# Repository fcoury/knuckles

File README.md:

# Knuckles

## Human Written TL;DR

There are a lot of split keyboards out there, but most of the ones that piqued
my interest don't have a number row, and I really like having one. I also
wanted a slim ergo split that feels somewhat like a Magic Keyboard. Knuckles is
my attempt at both.

## AI Assisted Details

Each half has 27 keys: a column-staggered 6×4 grid that includes the number row,
plus a three-key thumb fan. It uses Kailh PG1316S low-profile switches on
reversible footprints, a nice!nano controller, a JST-PH battery connector, and a
power switch. The controller area also fits the HolyKeebs TPS43 touchpad module.

The first wireless PCB was ordered from JLCPCB on 2025-03-02. The exact files
are archived in [`manufacturing/`](manufacturing/2026-10-18-knuckles-wireless-18.5mm/README.md).

`ergogen/config.yaml` also still defines the original wired `knuckles` board
(TRRS, small display). It's no longer supported. `knuckles_wireless` is the
board to build.

A separate [integrated nRF52840 revision](hardware/integrated-controller/README.md)
adds on-board USB, charging and radio circuitry in dedicated left/right layouts.
Its retained routed layouts and experimental firmware are engineering prototypes;
module sourcing, manufacturing review and bench validation remain release gates.
The normal build continues to use the nice!nano design.

## Build it

For assembly parts and quantities, see the [bill of materials](docs/bill-of-materials.md).

You'll need Node.js 18+ (CI uses Node 20) and Git. Footprints live in a
submodule, so clone recursively:

```sh
git clone --recursive https://github.com/fcoury/knuckles.git
cd knuckles
npm install
npm run build
```

`npm run build` runs Ergogen on `ergogen/config.yaml` and writes the PCBs,
plates, outlines, and bottom tray STL. `npm run debug` does the same with
Ergogen's debug output. `npm run watch:build` and `npm run watch:debug` rebuild
whenever the YAML or scripts change.

### Key spacing

The default is 18.5 mm center to center. That's the compact layout and the one
that was ordered. 19.5 mm is also available:

```sh
npm run build -- --spacing 19.5

# Keep both layouts side by side
npm run debug -- --spacing 18.5 --output build/18.5
npm run debug -- --spacing 19.5 --output build/19.5
```

Plates, holes, the silkscreen artwork, and the bottom tray all follow the
selected spacing. Run `npm run build -- --help` for all options. The
[gotchas](#gotchas) cover how spacing interacts with the other scripts.

## Full pipeline

The full pipeline also needs Docker. It runs KiCad 8, KiBot, and Freerouting in
containers, pulling the images on first run.

`./build.sh`:

1. Cleans previous outputs.
2. Runs Ergogen to generate the unrouted board and plates.
3. Exports renders and Gerbers for the plates and unrouted board with KiBot.
4. Exports a DSN, autoroutes it with Freerouting, and imports the SES back into KiCad.
5. Runs KiBot again on the autorouted board.

Other entry points:

- `./rebuild.sh` re-exports and autoroutes the boards already in `pcbs/`
  without running Ergogen.
- `npm run route` autoroutes only `knuckles_wireless`. It prunes dead-end
  traces and tries up to three times. A route is accepted only if KiCad reports
  no unconnected items, no dangling tracks, and no DRC errors.
- `./watch.sh` (macOS, needs `fswatch`) regenerates the PCB when the config
  changes and opens the result.

## Manufacturing

Upload the KiBot ZIP from `ergogen/output/gerbers/knuckles_wireless/` to
JLCPCB. Manufacturing output comes only from
`pcbs/knuckles_wireless_autorouted.kicad_pcb`. The KiBot configs
(`kibot/default.kibot.yaml`, `kibot/boards.kibot.yaml`) are tuned for JLCPCB.
The board uses a 0.25 mm copper-to-edge clearance for routed outlines.

Local builds and CI both route through `scripts/autoroute.sh`, with the same
KiCad image, Freerouting 2.1.0 JAR, rules, and optimizer settings. Freerouting
can still produce different trace geometry from run to run. That's why the
pipeline checks connectivity and DRC instead of comparing files byte for byte.

Each board that gets ordered goes in its own dated folder under
`manufacturing/`. Don't modify those files once they're archived.

## CI

`.github/workflows/build.yaml` runs the full pipeline for both spacings. Each
run uploads a `knuckles-18.5mm` and a `knuckles-19.5mm` artifact containing
cases, Gerbers, images, outlines, and PCBs. `npm test` runs real builds of both
layouts and checks spacing selection, the generated outputs, and rejection of
invalid values.

## Customizing

Everything starts in `ergogen/config.yaml`:

- **Layout:** the key matrix and thumb fan are under `points.zones.*`
  (spacing, splay, stagger).
- **Switches:** set `meta.footprint` and pick a preset (`mx`, `choc_v1`,
  `choc_v2`, or the low-profile reversible footprints).
- **Wiring:** column and row nets are assigned per zone. MCU pins are mapped in
  the `mcu` footprint section.
- **Touchpad:** the TPS43 adapter sits on top of the nice!nano and uses its
  VCC, GND, SDA, and SCL pins, so the PCB doesn't need its own touchpad
  footprint.
- **Case:** edit `cases/knuckles_bottom_tray.jscad` and the
  `outlines/_bottom_case*` outlines to change walls and cutouts.

KiCad project settings in `pcbs/` are generated, so edit
`kicad/projects/knuckles_wireless.kicad_pro` instead. The build copies it next
to the board.

The silkscreen badge and wordmark are documented in
[`artwork/knuckles/`](artwork/knuckles/README.md).

## Repository layout

| Path | Contents |
| --- | --- |
| `docs/` | Assembly reference, starting with the bill of materials |
| `ergogen/` | Ergogen config, footprints submodule, generated images and Gerbers |
| `pcbs/` | Generated KiCad boards and plates; `autoroute/<board>/` holds DSN, SES, router log, and DRC report |
| `outlines/` | DXF/SVG outlines for the PCB, plates, and case |
| `cases/` | JSCAD bottom tray and generated STL; `thin/` has slim case prototypes for older 18.5 mm boards |
| `kicad/projects/` | Canonical KiCad project settings |
| `kibot/` | KiBot configs and DSN/SES helper scripts |
| `freerouting/` | Autorouter rules and JAR |
| `hardware/integrated-controller/` | Opt-in integrated controller PCB and firmware prototypes, routed layouts and engineering checks |
| `manufacturing/` | Archived files for each ordered board |
| `artwork/` | Badge and wordmark sources and PCB renders |
| `images/` | Reference renders of the plates and controller overlay |
| `scripts/` | Build, autoroute, artwork, and case scripts |

## Gotchas

- `--spacing` overrides `KNUCKLES_SPACING`, which overrides the config
  default. The YAML is never rewritten. `pcbs/build-info.json` records which
  spacing was used.
- Changing spacing means you need matching plates and a matching case. Don't
  mix routed boards or Gerbers from different spacing builds.
- `./build.sh` (`KNUCKLES_SPACING=19.5 ./build.sh`) always writes to the root
  output folders. Use `npm run build -- --output` if you want them kept apart.
- `./rebuild.sh` routes whatever board is already in `pcbs/` and keeps its
  spacing.
- `ergogen/output/pcbs/` contains old snapshots that builds don't update.

## License

MIT. See [`LICENSE`](LICENSE).

## Credits

- [Ergogen](https://github.com/ergogen/ergogen) and its community.
- Footprints from [ceoloide](https://github.com/ceoloide/ergogen-footprints)
  (`ergogen/footprints/ceoloide`) and related authors.
- Freerouting for autorouting, KiBot and PCBDraw for renders and exports.

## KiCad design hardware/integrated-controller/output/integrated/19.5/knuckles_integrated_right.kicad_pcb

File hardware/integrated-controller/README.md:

# Knuckles integrated controller — revision 0.2 engineering study

This revision integrates an nRF52840 radio module, USB-C, battery charging and
3.3 V regulation into dedicated left and right keyboard PCBs. It retains
27 keys per half and the right-hand TPS43. The default spacing is **18.5 mm**;
19.5 mm is generated from the same sources.

**These are engineering prototypes and have not been manufactured or tested.** The
firmware artifacts are experimental builds for the new circuit. Do not flash
them onto the working nice!nano keyboards or order these PCB files.

## Inspect the design

Open the routed boards in KiCad 8:

- [18.5 mm left routed](output/routed/18.5/left/knuckles_integrated_left.kicad_pro)
- [18.5 mm right routed](output/routed/18.5/right/knuckles_integrated_right.kicad_pro)
- [19.5 mm left routed](output/routed/19.5/left/knuckles_integrated_left.kicad_pro)
- [19.5 mm right routed](output/routed/19.5/right/knuckles_integrated_right.kicad_pro)

The complete schematic/generator projects remain separate:

- [18.5 mm left](output/integrated/18.5/knuckles_integrated_left.kicad_pro)
- [18.5 mm right](output/integrated/18.5/knuckles_integrated_right.kicad_pro)
- [19.5 mm left](output/integrated/19.5/knuckles_integrated_left.kicad_pro)
- [19.5 mm right](output/integrated/19.5/knuckles_integrated_right.kicad_pro)

These generator projects contain fixed power/USB/ground cells and open remaining
connections. The completed native layouts and their measured acceptance state are
separate under `output/routed/<spacing>/<hand>/summary.json`.

Each project includes the controller, power circuit and complete 27-key matrix
schematic. The native schematic references match the PCB. The separate
[45 × 55 mm controller study](output/knuckles_controller.kicad_pro) remains
available for electrical review; building a separate daughterboard is optional.

See [the engineering review and routing handoff](ENGINEERING.md),
[charging/bootloader build instructions](firmware/README.md),
[physical GPIO map](output/pin-map.json), and [component review BOM](output/bom-review.csv).
The BOM is for the controller study; it is **not** a keyboard manufacturing BOM.

## Decisions implemented

- Raytac MDBT50Q-1MV2 with calibrated internal low-frequency RC clock. The module
  provides the 32 MHz crystal, RF matching and antenna; there is no nice!nano.
- BQ25186 programmable charger and power path, followed by TPS63031 fixed 3.3 V
  buck-boost regulation. Independent PMIC and touchpad I2C buses.
- Protected 1S 4.2 V LiPo packs, from 110 through 500 mAh. The battery lives in
  the case, clear of the antenna; capacity alone does not specify dimensions.
- Charging profiles: 110 mAh / 20 mA; 250 mAh / 50 mA; 500 mAh / 100 mA.
  A different capacity requires a reviewed profile; the board cannot detect mAh.
- Charging is disabled in the default firmware **and** R12 is unpopulated.
  Enabling it requires the actual cell specification and a cell-mounted 10 kΩ,
  beta-3435 thermistor. J2 is battery power; J6 is the separate thermistor pair.
- Right half is the split central and USB/Bluetooth mouse/keyboard. Left sends
  its keys over BLE and uses a separate USB CDC function to negotiate charging.
- Four copper layers and a 1.6 mm board. Several small components and SWD pads
  are on the back, so assembly needs two sides. These placements remain subject
  to routing and case review.
- A case-mounted TPS43 holder replaces the two old controller cover holes.
  Its proposed position moves roughly 7 mm toward USB to clear the radio area.
  The five main case mounting holes remain.

## Rebuild and verify

From the repository root, with Node dependencies and Docker available:

```sh
npm run build:integrated
npm run build:integrated -- --spacing 19.5
npm run check:integrated
npm test
```

`build:integrated` starts from fresh Ergogen output and composes both halves.
It adds fixed local power and USB routes, without overwriting the normal PCB
outputs or generating Gerbers.
`check:integrated` exports ERC, DRC and netlists using pinned KiCad 8, compares
schematic nets with physical pads, and checks the matrix/power contracts.
It deliberately reports unconnected nets separately; passing is a placement
and electrical-consistency checkpoint, not fabrication clearance.

The retained [validation summary](output/validation-summary.json) records each
board's errors, warnings and unrouted connections. Retained routed warnings
include silkscreen/library details and dangling-track/via reports; these need
review before release, including ground-stitch intent after plane filling.

`circuit.py` is the controller electrical source. `integrate.py` contains the
initial placement and mechanical policy. `keyboard_schematic.py` adds the matrix
hierarchy. `generate.py` creates the controller sheets and custom lands.
`vendor-footprints.py` runs in the pinned KiCad image when adding standard lands.
`check-parts.py` refreshes catalog snapshots without buying or reserving parts.

Run the remaining outer-layer routing separately (both hands and spacings):

```sh
python3 hardware/integrated-controller/route-remaining.py --hand right --spacing 18.5
python3 hardware/integrated-controller/route-remaining.py --hand left --spacing 18.5
```

Repeat with `--spacing 19.5` for that geometry. `--fanout` enables the SMD
escape pre-pass; `--resume` continues a candidate. The pinned Freerouting JVM
writes disposable candidates under `output/candidates/<spacing>/<hand>/`.
A failed candidate remains available for inspection and exits nonzero.
Manual routing may still be required. These runs preserve the completed native
KiCad files under `output/routed/`, which are the authoritative finished layouts;
the generator rebuilds only the separate partial source projects.

Validate all four native layouts without rerouting:

```sh
npm run check:integrated:routed
```

This checks footprint positions/nets, protected routes, physical DRC, airwires,
USB ground coverage and via/paste intersections. Results are retained in
[the routed validation summary](output/routed/validation-summary.json).
The selected 3313 stack and calculator inputs are retained in
[stackup.json](references/stackup.json).

Export a completed native layout’s engineering-review files with:

```sh
python3 hardware/integrated-controller/export-review.py --hand right --spacing 18.5
```

This rechecks DRC, ground coverage and via/paste intersections before writing
Gerbers/drills, a controller-only BOM and a CPL draft under
`output/manufacturing-review/`. Rotations, stencil, sourcing, mechanics and bench
behavior still need review. The package is explicitly not approved for ordering.

## Remaining release gates

1. Secure the radio module. JLC's saved C5118826 listing has **zero stock**;
   consignment/global sourcing or a reviewed substitute still needs a quote.
2. Review the completed routing, ground planes, USB transitions, thermal vias
   and fabrication rules with the manufacturer. All four retained layouts pass
   zero-airwire/zero-physical-error checks; impedance and DFM remain review gates.
3. Confirm the touchpad, battery, connector/cable, switch and keycap clearances
   with a full-size print or mechanical prototype. Battery size is unresolved.
4. Bench-test supply startup/transients, idle/suspend current, SWD/UF2 recovery,
   both keyboard halves and TPS43, and charging/NTC behavior before fitting R12.
5. Complete manufacturing BOM/CPL, orientation review, module sourcing and USB
   product identification before release. No order or programming was performed.

## References and attribution

Manufacturer and upstream sources are recorded in [sources.json](sources.json).
Standard footprints are from KiCad 8 under
[CC BY-SA 4.0 with the KiCad library exception](https://www.kicad.org/libraries/license/).
The Alps SSSS811101 land derives from the repository's ceoloide footprint,
copyright Marco Massarelli 2023, with attribution to infused-kim and ceoloide,
under CC-BY-NC-SA-4.0. Its pad geometry was checked against Alps drawings.
The TI charger and ALPS reset lands follow the manufacturer drawings. Keyboard
switch, diode and artwork geometry retain the source repository's licenses.

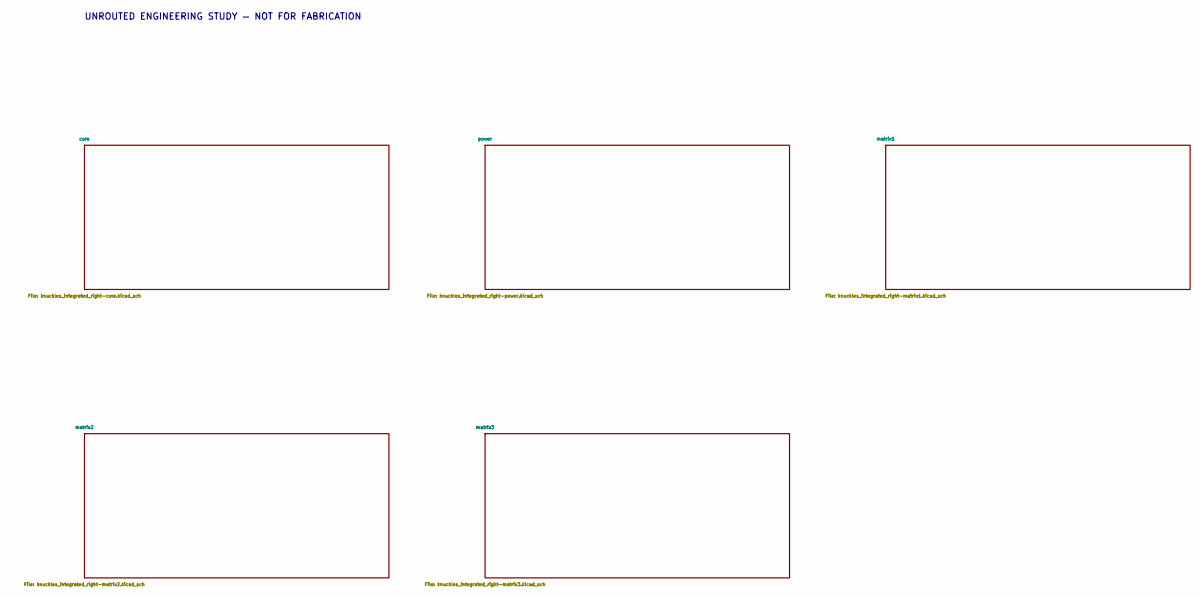
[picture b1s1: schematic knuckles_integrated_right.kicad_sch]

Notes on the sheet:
UNROUTED ENGINEERING STUDY — NOT FOR FABRICATION

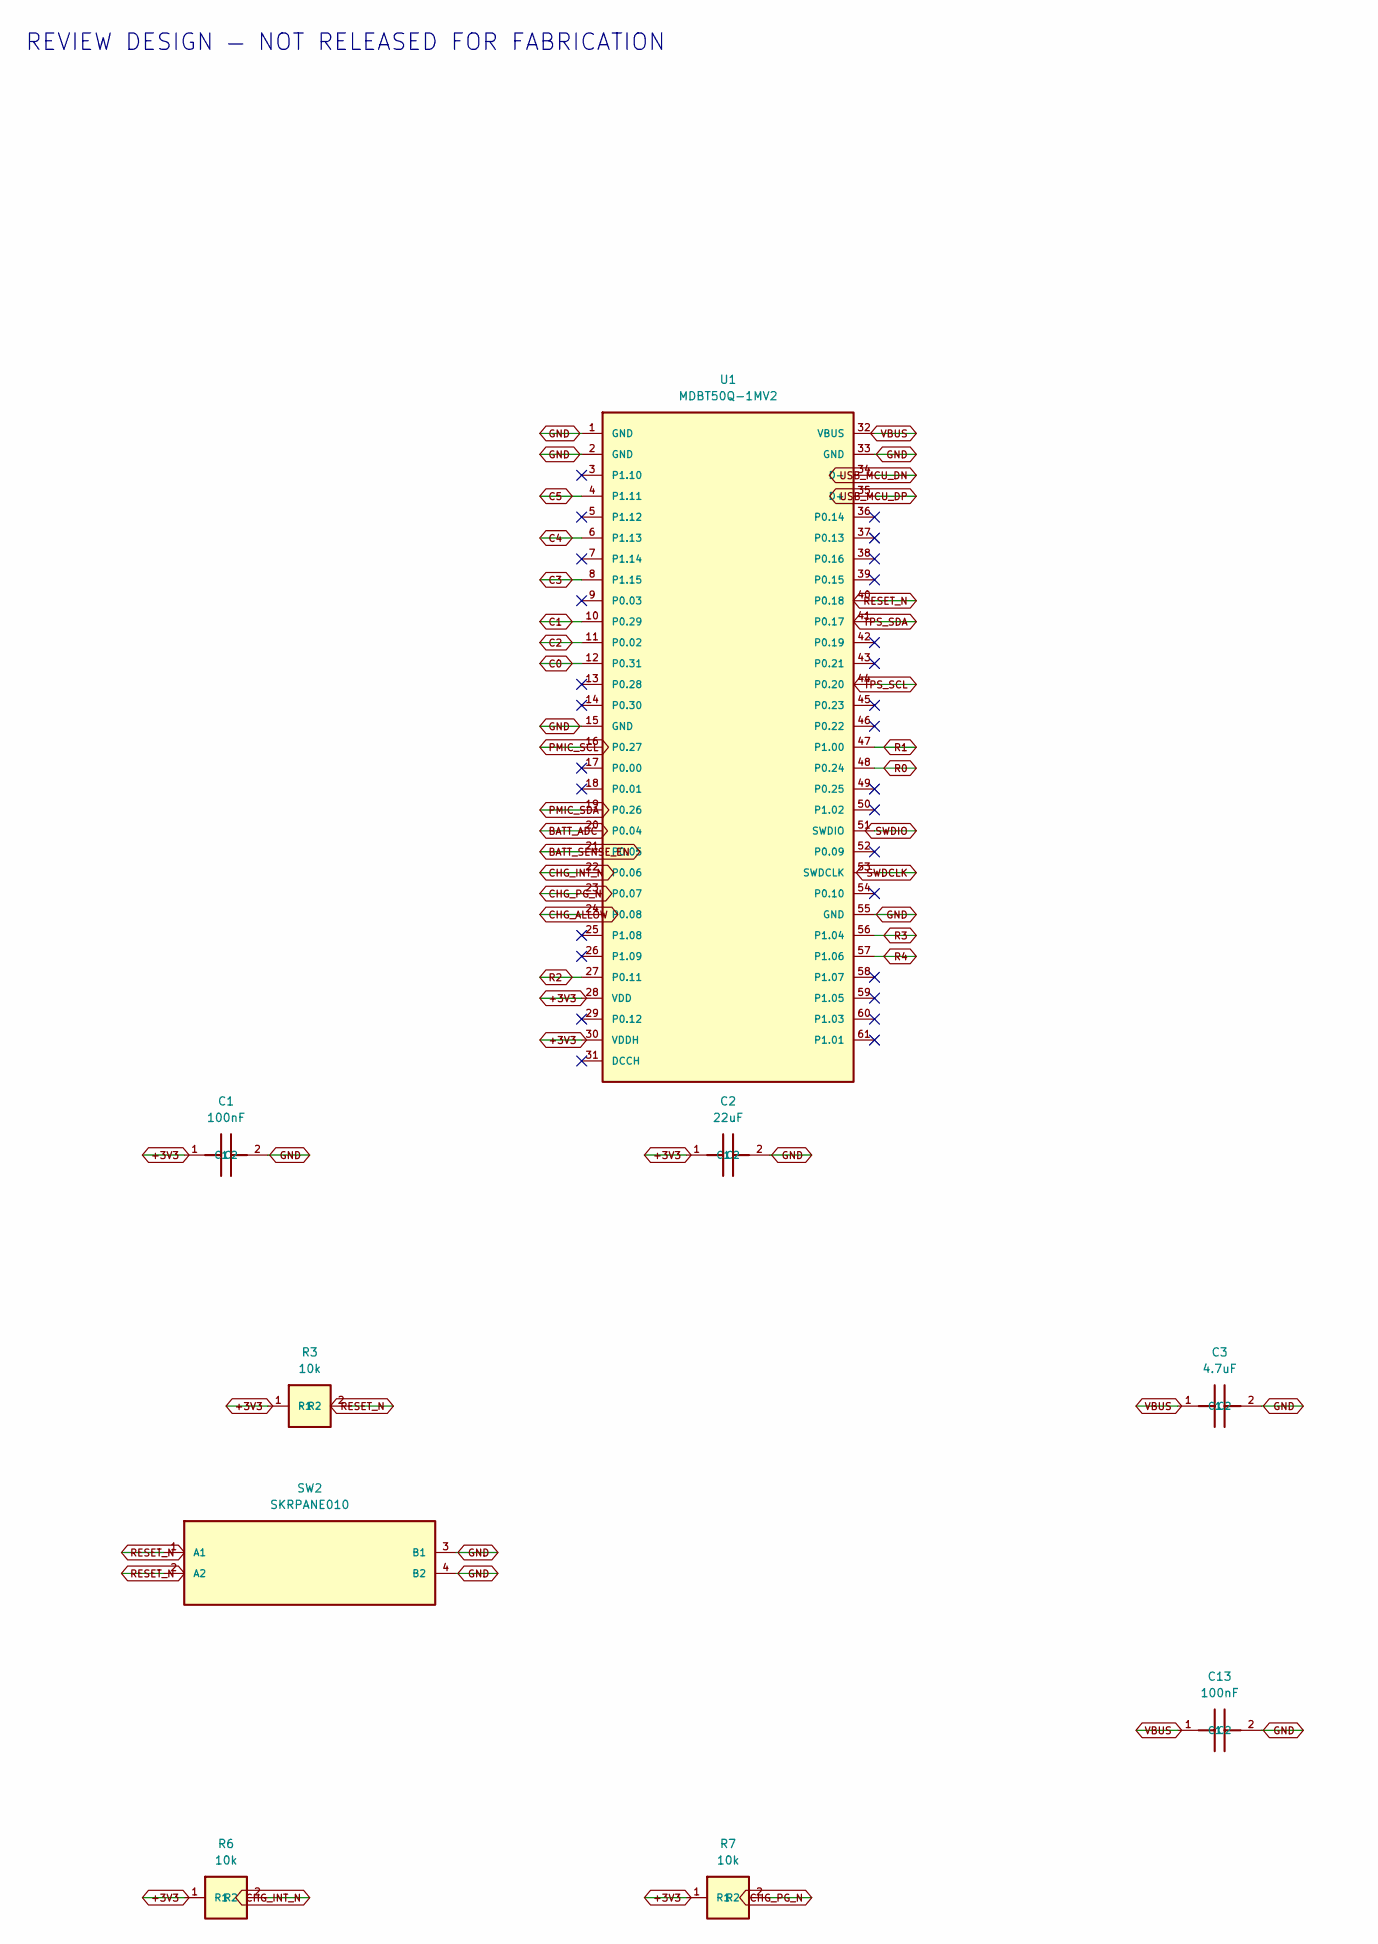
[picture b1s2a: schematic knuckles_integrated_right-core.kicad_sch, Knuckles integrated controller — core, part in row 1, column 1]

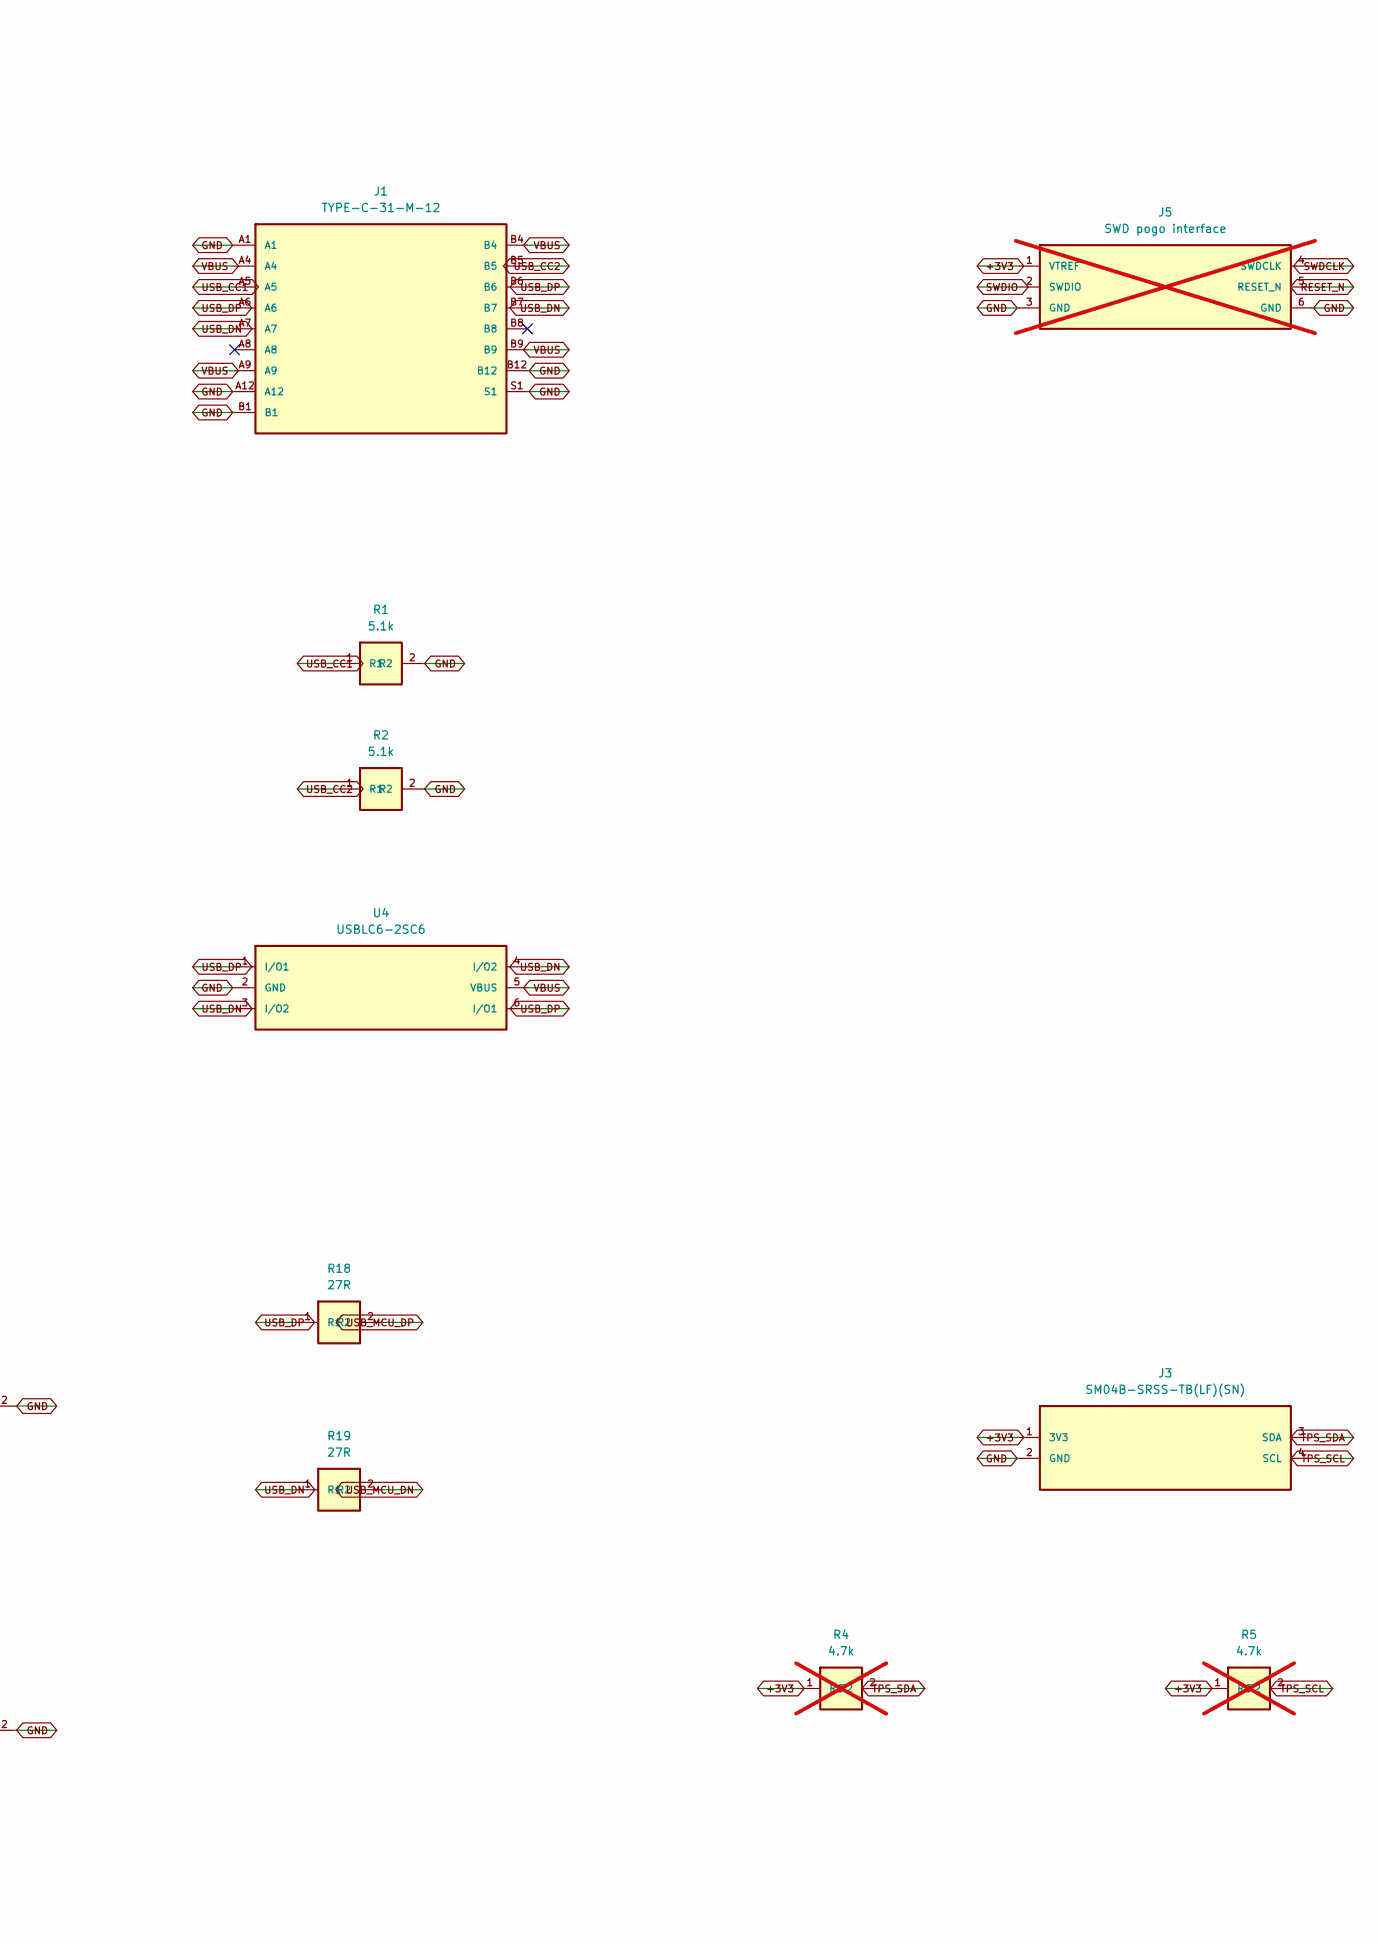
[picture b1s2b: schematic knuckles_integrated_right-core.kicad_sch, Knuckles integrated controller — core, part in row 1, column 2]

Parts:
C1, C13: 100nF; C_0603_1608Metric; LCSC C14663
C2: 22uF; C_0805_2012Metric; LCSC C45783
C3: 4.7uF; C_0603_1608Metric; LCSC C19666
J1: TYPE-C-31-M-12; USB_C_Receptacle_HRO_TYPE-C-31-M-12; LCSC C165948
J3: SM04B-SRSS-TB(LF)(SN); JST_SH_SM04B-SRSS-TB_1x04-1MP_P1.00mm_Horizontal; LCSC C160404
J5: SWD pogo interface; SWD_2x3_P1.27_NoHoles; not fitted
R1, R2: 5.1k; R_0603_1608Metric; LCSC C23186
R3, R6, R7: 10k; R_0603_1608Metric; LCSC C25804
R4, R5: 4.7k; R_0603_1608Metric; LCSC C23162; not fitted
R18, R19: 27R; R_0603_1608Metric; LCSC C25190
SW2: SKRPANE010; LCSC C470426
U1: MDBT50Q-1MV2; Raytac_MDBT50Q; LCSC C5118826
U4: USBLC6-2SC6; SOT-23-6; LCSC C7519

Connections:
+3V3: C1.1 (C1), C2.1 (C1), J3.1 (3V3), J5.1 (VTREF), R3.1 (R1), R4.1 (R1), R5.1 (R1), R6.1 (R1), R7.1 (R1), U1.28 (VDD), U1.30 (VDDH); also elsewhere on the board
BATT_ADC: U1.20 (P0.04); also elsewhere on the board
BATT_SENSE_EN: U1.21 (P0.05); also elsewhere on the board
C0: U1.12 (P0.31); also elsewhere on the board
C1: U1.10 (P0.29); also elsewhere on the board
C2: U1.11 (P0.02); also elsewhere on the board
C3: U1.8 (P1.15); also elsewhere on the board
C4: U1.6 (P1.13); also elsewhere on the board
C5: U1.4 (P1.11); also elsewhere on the board
CHG_ALLOW: U1.24 (P0.08); also elsewhere on the board
CHG_INT_N: R6.2 (R2), U1.22 (P0.06); also elsewhere on the board
CHG_PG_N: R7.2 (R2), U1.23 (P0.07); also elsewhere on the board
GND: C1.2 (C2), C2.2 (C2), C3.2 (C2), C13.2 (C2), J1.A1, J1.A12, J1.B1, J1.B12, J1.S1, J3.2 (GND), J5.3 (GND), J5.6 (GND), R1.2 (R2), R2.2 (R2), SW2.3 (B1), SW2.4 (B2), U1.1 (GND), U1.2 (GND), U1.15 (GND), U1.33 (GND), U1.55 (GND), U4.2 (GND); also elsewhere on the board
PMIC_SCL: U1.16 (P0.27); also elsewhere on the board
PMIC_SDA: U1.19 (P0.26); also elsewhere on the board
R0: U1.48 (P0.24); also elsewhere on the board
R1: U1.47 (P1.00); also elsewhere on the board
R2: U1.27 (P0.11); also elsewhere on the board
R3: U1.56 (P1.04); also elsewhere on the board
R4: U1.57 (P1.06); also elsewhere on the board
RESET_N: J5.5 (RESET_N), R3.2 (R2), SW2.1 (A1), SW2.2 (A2), U1.40 (P0.18)
SWDCLK: J5.4 (SWDCLK), U1.53 (SWDCLK)
SWDIO: J5.2 (SWDIO), U1.51 (SWDIO)
TPS_SCL: J3.4 (SCL), R5.2 (R2), U1.44 (P0.20)
TPS_SDA: J3.3 (SDA), R4.2 (R2), U1.41 (P0.17)
USB_CC1: J1.A5, R1.1 (R1)
USB_CC2: J1.B5, R2.1 (R1)
USB_DN: J1.A7, J1.B7, R19.1 (R1), U4.3 (I/O2), U4.4 (I/O2)
USB_DP: J1.A6, J1.B6, R18.1 (R1), U4.1 (I/O1), U4.6 (I/O1)
USB_MCU_DN: R19.2 (R2), U1.34 (D-)
USB_MCU_DP: R18.2 (R2), U1.35 (D+)
VBUS: C3.1 (C1), C13.1 (C1), J1.A4, J1.A9, J1.B4, J1.B9, U1.32 (VBUS), U4.5 (VBUS); also elsewhere on the board

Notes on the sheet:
REVIEW DESIGN — NOT RELEASED FOR FABRICATION

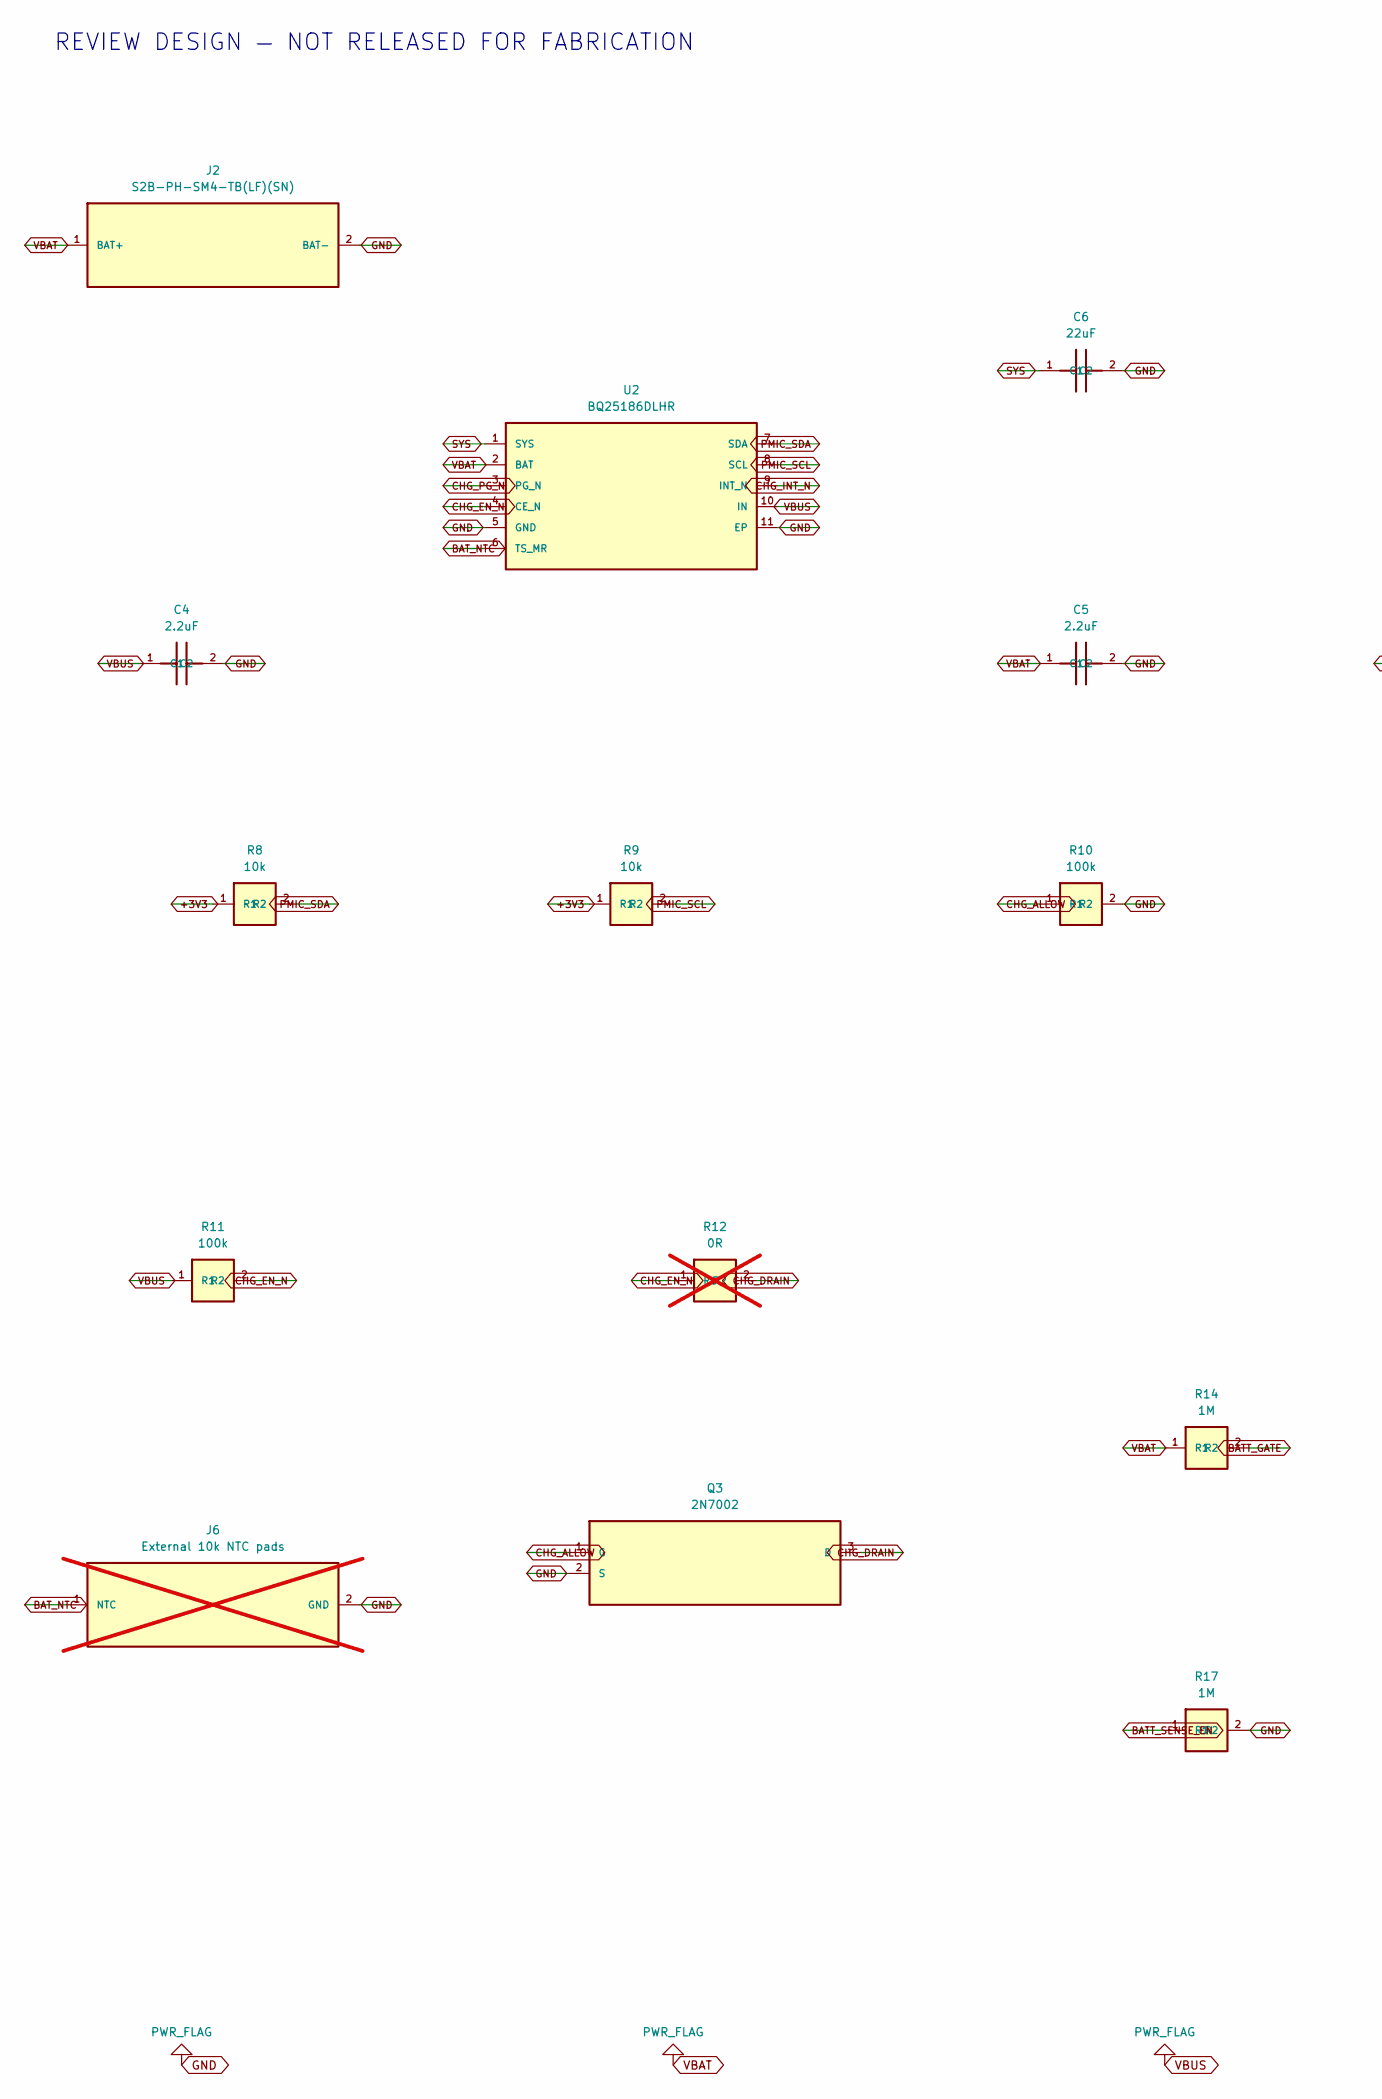
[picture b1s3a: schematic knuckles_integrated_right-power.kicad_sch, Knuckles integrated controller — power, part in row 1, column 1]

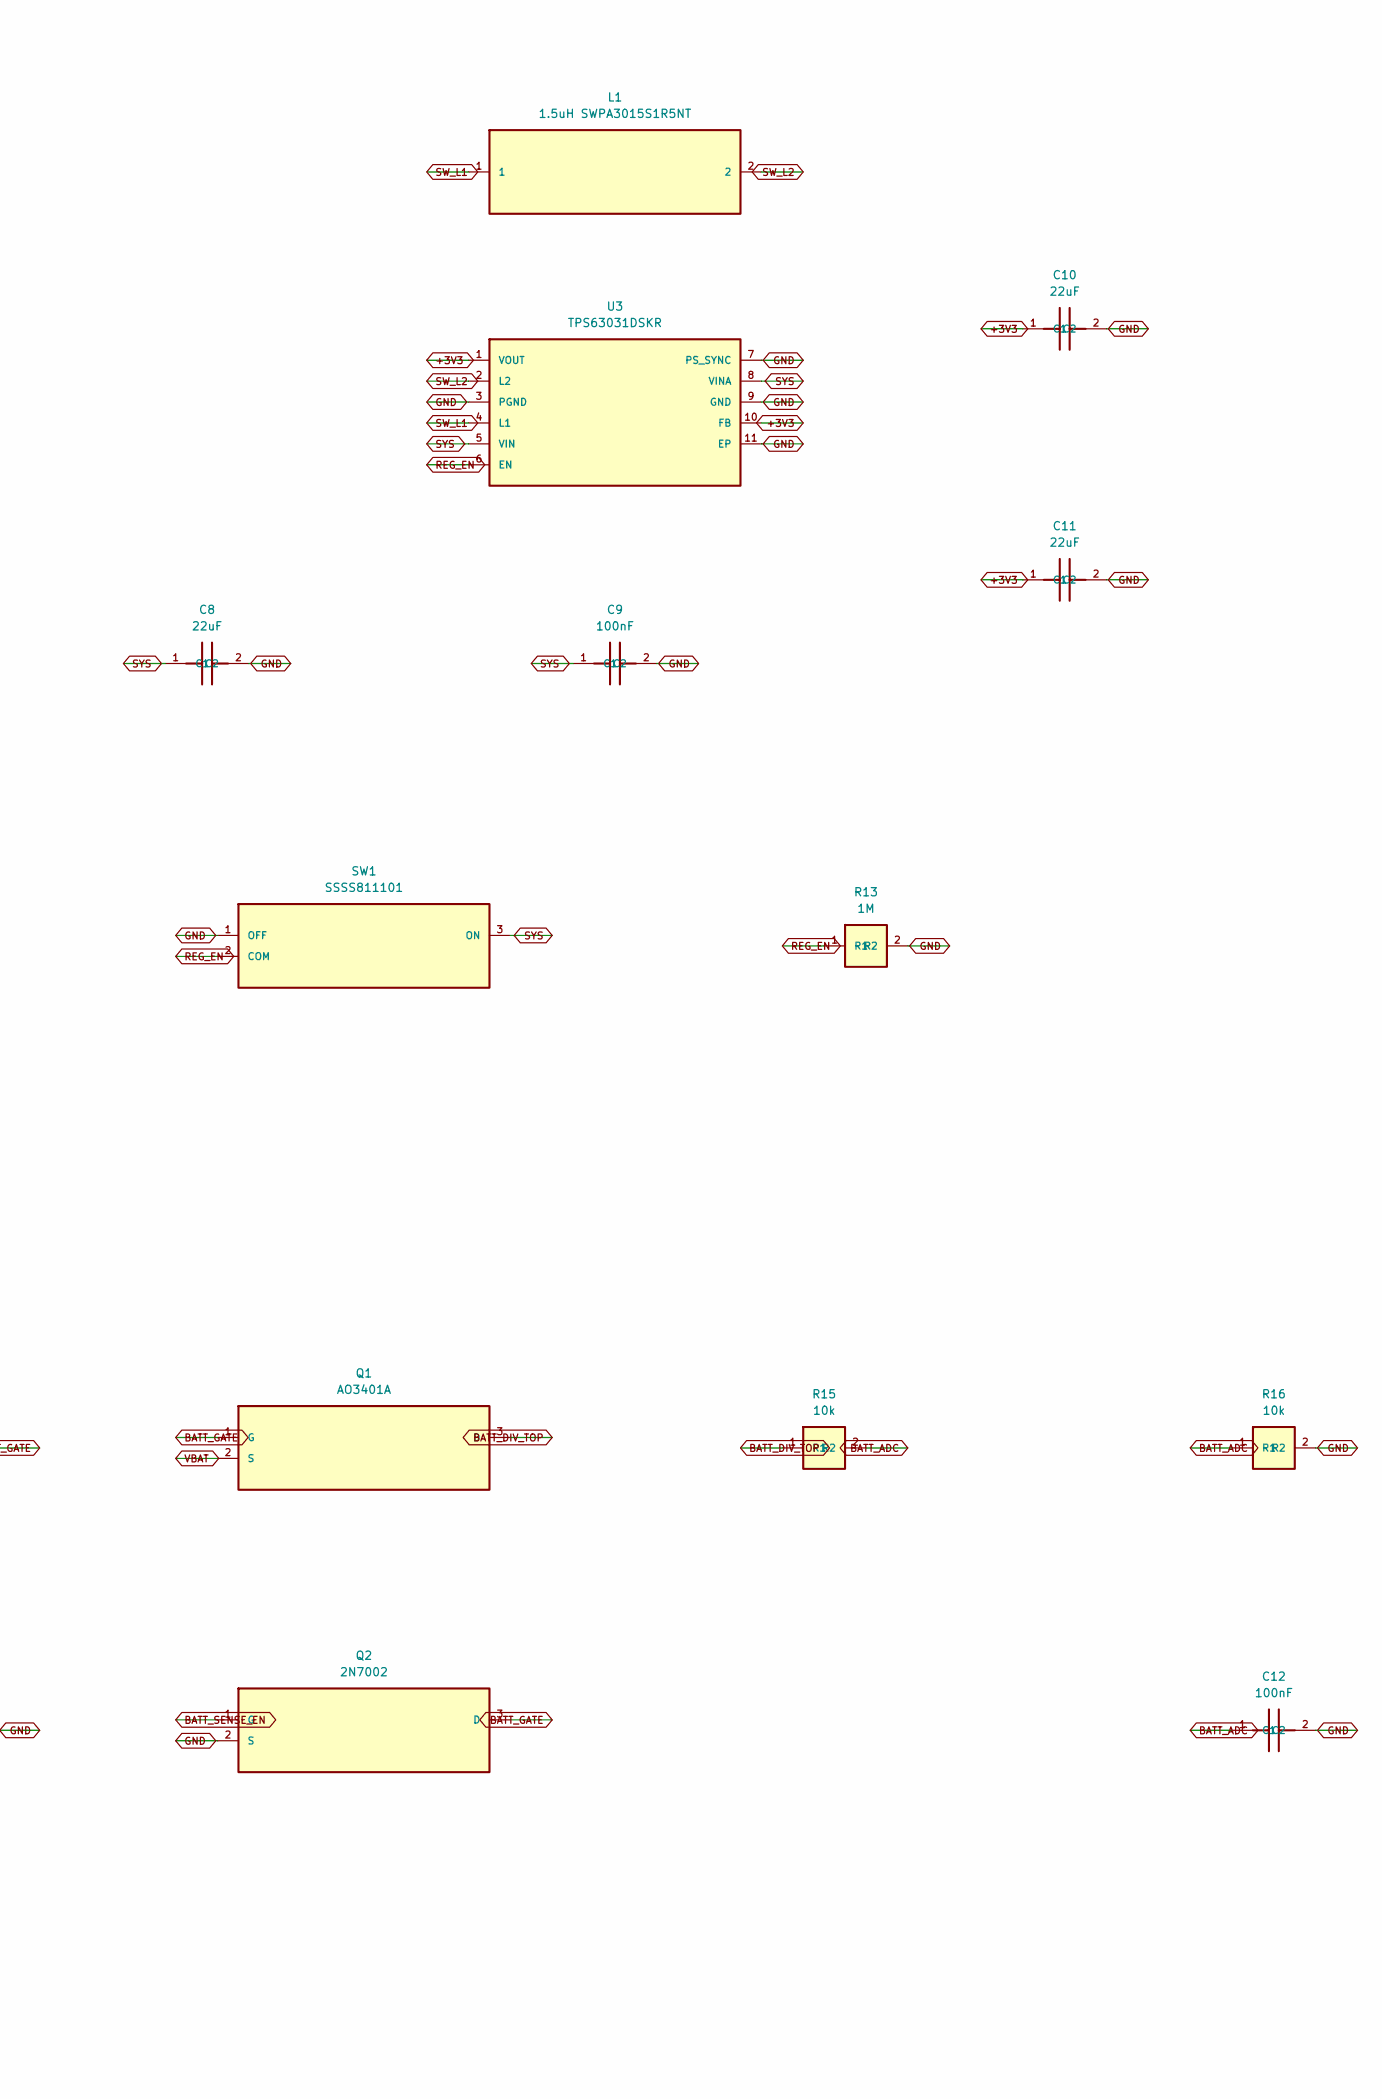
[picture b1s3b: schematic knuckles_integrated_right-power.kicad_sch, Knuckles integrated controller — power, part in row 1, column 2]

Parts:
C4, C5: 2.2uF; C_0603_1608Metric; LCSC C23630
C6, C8, C10, C11: 22uF; C_0805_2012Metric; LCSC C45783
C9, C12: 100nF; C_0603_1608Metric; LCSC C14663
J2: S2B-PH-SM4-TB(LF)(SN); JST_PH_S2B-PH-SM4-TB_1x02-1MP_P2.00mm_Horizontal; LCSC C295747
J6: External 10k NTC pads; NTC_WirePads; not fitted
L1: 1.5uH SWPA3015S1R5NT; L_Sunlord_SWPA3015S; LCSC C56594
Q1: AO3401A; SOT-23; LCSC C15127
Q2, Q3: 2N7002; SOT-23; LCSC C8545
R8, R9, R15, R16: 10k; R_0603_1608Metric; LCSC C25804
R10, R11: 100k; R_0603_1608Metric; LCSC C25803
R12: 0R; R_0603_1608Metric; LCSC C21189; not fitted
R13, R14, R17: 1M; R_0603_1608Metric; LCSC C22935
SW1: SSSS811101; LCSC C109335
U2: BQ25186DLHR; TI_WSON_DLH0010A; LCSC C44639442
U3: TPS63031DSKR; WSON-10-1EP_2.5x2.5mm_P0.5mm_EP1.2x2mm; LCSC C15516

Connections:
+3V3: C10.1 (C1), C11.1 (C1), R8.1 (R1), R9.1 (R1), U3.1 (VOUT), U3.10 (FB); also elsewhere on the board
BATT_ADC: C12.1 (C1), R15.2 (R2), R16.1 (R1); also elsewhere on the board
BATT_DIV_TOP: Q1.3 (D), R15.1 (R1)
BATT_GATE: Q1.1 (G), Q2.3 (D), R14.2 (R2)
BATT_SENSE_EN: Q2.1 (G), R17.1 (R1); also elsewhere on the board
BAT_NTC: J6.1 (NTC), U2.6 (TS_MR)
CHG_ALLOW: Q3.1 (G), R10.1 (R1); also elsewhere on the board
CHG_DRAIN: Q3.3 (D), R12.2 (R2)
CHG_EN_N: R11.2 (R2), R12.1 (R1), U2.4 (CE_N)
CHG_INT_N: U2.9 (INT_N); also elsewhere on the board
CHG_PG_N: U2.3 (PG_N); also elsewhere on the board
GND: C4.2 (C2), C5.2 (C2), C6.2 (C2), C8.2 (C2), C9.2 (C2), C10.2 (C2), C11.2 (C2), C12.2 (C2), J2.2 (BAT-), J6.2 (GND), Q2.2 (S), Q3.2 (S), R10.2 (R2), R13.2 (R2), R16.2 (R2), R17.2 (R2), SW1.1 (OFF), U2.5 (GND), U2.11 (EP), U3.3 (PGND), U3.7 (PS_SYNC), U3.9 (GND), U3.11 (EP); also elsewhere on the board
PMIC_SCL: R9.2 (R2), U2.8 (SCL); also elsewhere on the board
PMIC_SDA: R8.2 (R2), U2.7 (SDA); also elsewhere on the board
REG_EN: R13.1 (R1), SW1.2 (COM), U3.6 (EN)
SW_L1: L1.1, U3.4 (L1)
SW_L2: L1.2, U3.2 (L2)
SYS: C6.1 (C1), C8.1 (C1), C9.1 (C1), SW1.3 (ON), U2.1 (SYS), U3.5 (VIN), U3.8 (VINA)
VBAT: C5.1 (C1), J2.1 (BAT+), Q1.2 (S), R14.1 (R1), U2.2 (BAT)
VBUS: C4.1 (C1), R11.1 (R1), U2.10 (IN); also elsewhere on the board

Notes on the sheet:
REVIEW DESIGN — NOT RELEASED FOR FABRICATION
